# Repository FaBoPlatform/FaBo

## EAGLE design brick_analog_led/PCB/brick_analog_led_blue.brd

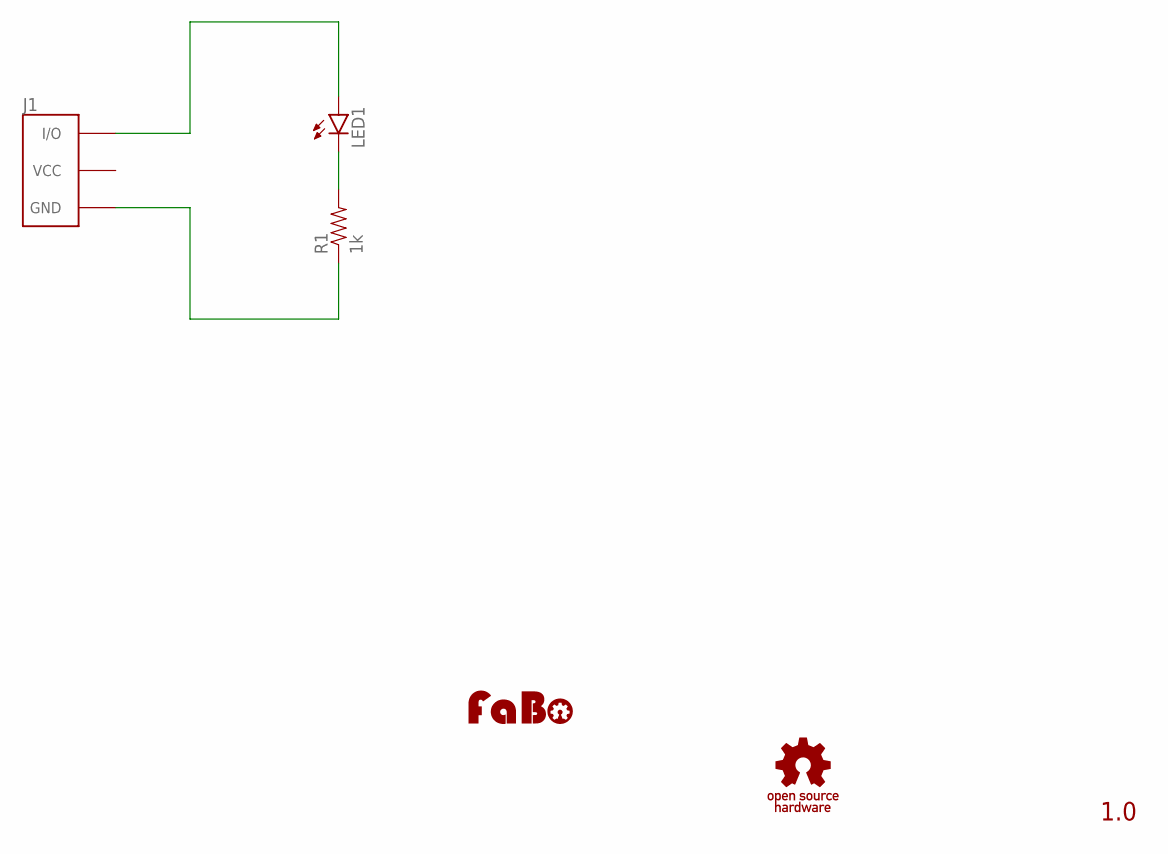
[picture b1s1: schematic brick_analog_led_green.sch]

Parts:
J1: BRICK_3PIN_NORMAL; BRICK_3PIN
LED1: LED-5MM
R1: 1k; RES-AXL-REGULAR
U$1: LOGO_FABO-M; LOGO_FABO_M
U$4: LOGO_OSHW_T-M; LOGO_OSHW_T_M

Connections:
GND: J1.GND, R1.P$1 (1)
unnamed: J1.IN/OUT (I/O), LED1.A
unnamed: LED1.K (C), R1.P$2 (2)

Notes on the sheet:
1.0

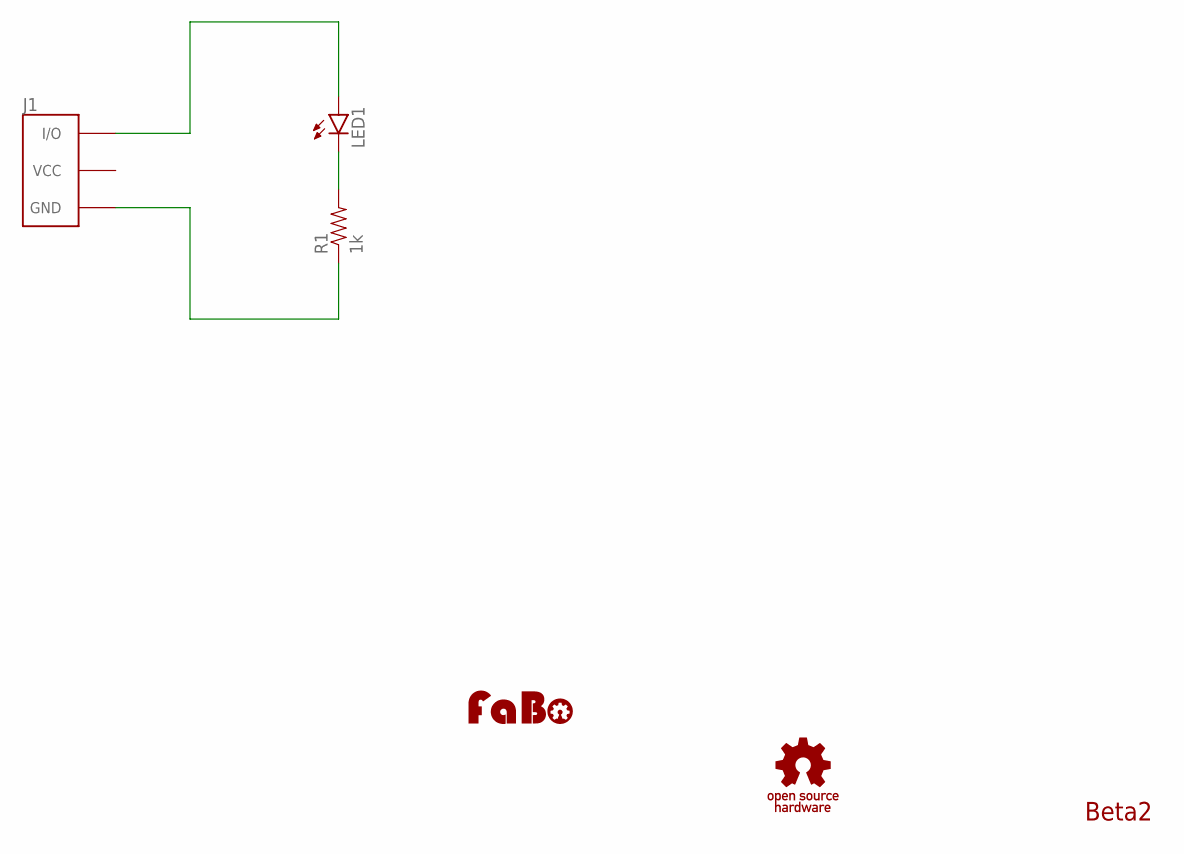
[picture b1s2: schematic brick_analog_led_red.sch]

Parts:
J1: BRICK_3PIN
LED1: LED-5MM
R1: 1k; RES-AXL-REGULAR
U$1: LOGO_FABO-M; LOGO_FABO_M
U$4: LOGO_OSHW_T-M; LOGO_OSHW_T_M

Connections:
GND: J1.GND, R1.P$1 (1)
unnamed: J1.IN/OUT (I/O), LED1.A
unnamed: LED1.K (C), R1.P$2 (2)

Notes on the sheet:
Beta2

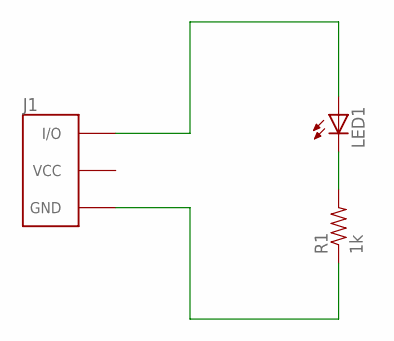
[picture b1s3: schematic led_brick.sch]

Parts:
J1: BRICK_3PIN
LED1: LED; LED5MM
R1: 1k; AXIAL-0.4

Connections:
GND: J1.GND, R1.P$1 (1)
unnamed: J1.IN/OUT (I/O), LED1.A
unnamed: LED1.K (C), R1.P$2 (2)

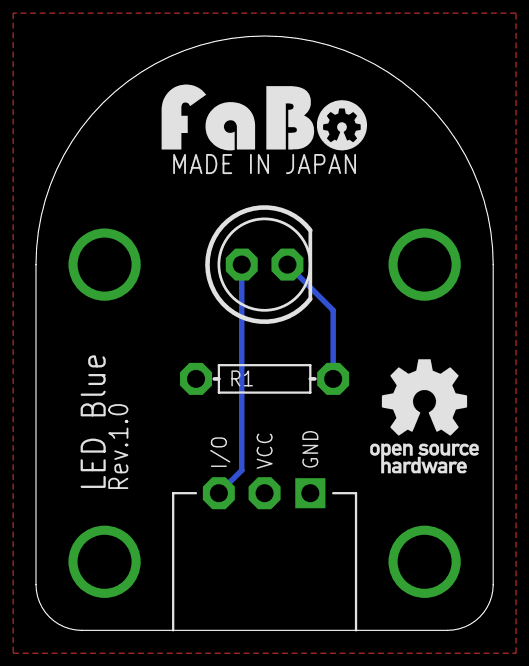
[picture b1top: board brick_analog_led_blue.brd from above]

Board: 2 copper layers, 25.4 x 33.0 mm, 5 parts (0 on the bottom side), 3 nets.

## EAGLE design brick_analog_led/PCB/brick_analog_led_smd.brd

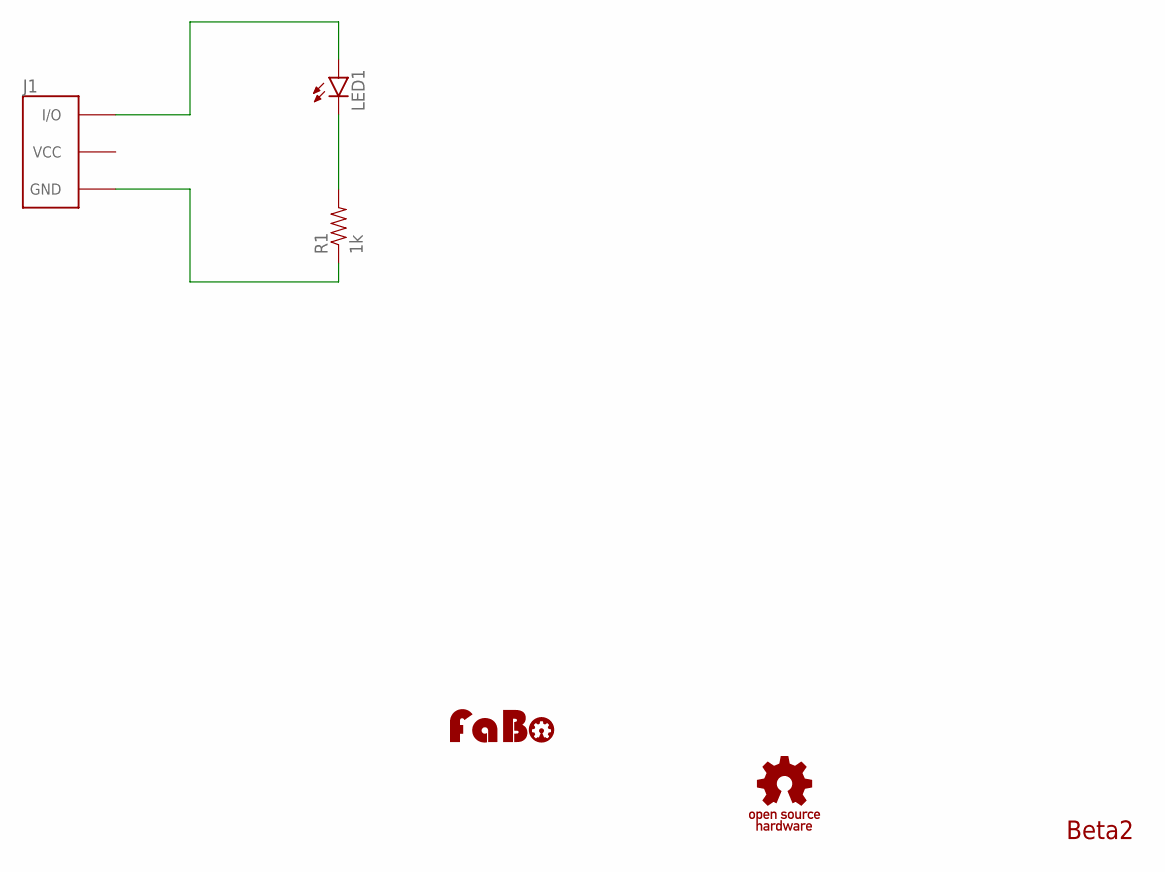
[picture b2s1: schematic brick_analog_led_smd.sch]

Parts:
J1: BRICK_3PIN
LED1: LED-EIA0603; EIA0603-LED
R1: 1k; EIA0603
U$2: LOGO_FABO-M; LOGO_FABO_M
U$4: LOGO_OSHW_T-M; LOGO_OSHW_T_M

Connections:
GND: J1.GND, R1.1
unnamed: J1.IN/OUT (I/O), LED1.A
unnamed: LED1.C, R1.2

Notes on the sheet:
Beta2

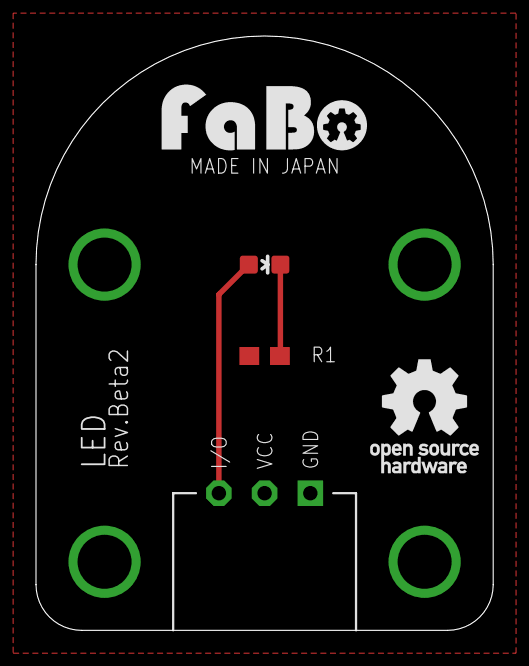
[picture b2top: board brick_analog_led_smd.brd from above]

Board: 2 copper layers, 25.4 x 33.0 mm, 5 parts (0 on the bottom side), 3 nets.

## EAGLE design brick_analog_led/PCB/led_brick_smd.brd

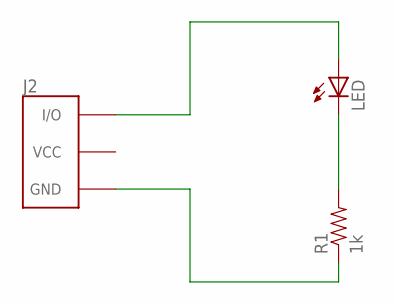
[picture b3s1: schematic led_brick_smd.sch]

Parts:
J2: BRICK_3PIN
LED: LED; CHIP-LED0603
R1: 1k; 0603-RES

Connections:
GND: J2.GND, R1.1
unnamed: J2.IN/OUT (I/O), LED.A
unnamed: LED.C, R1.2

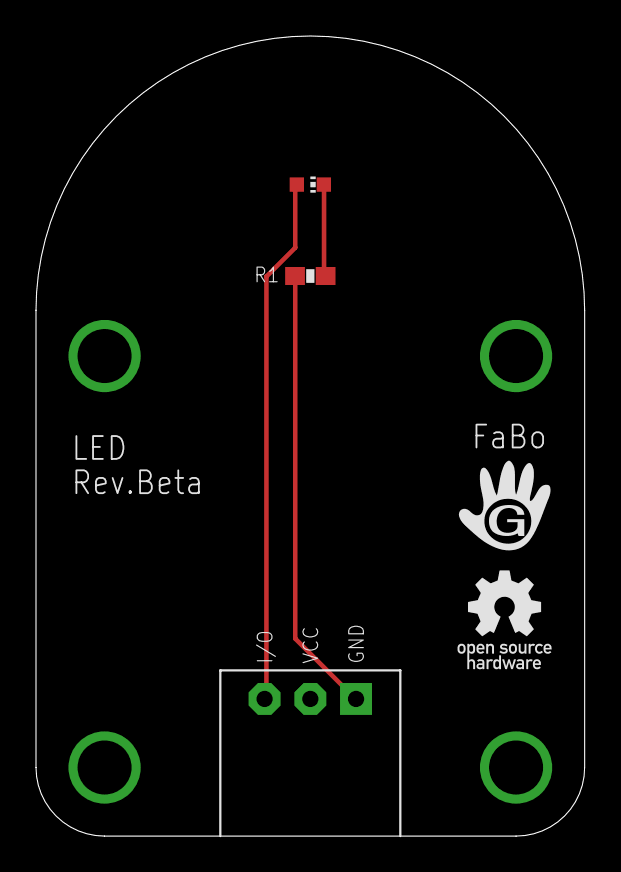
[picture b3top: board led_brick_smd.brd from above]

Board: 2 copper layers, 30.5 x 44.5 mm, 5 parts (0 on the bottom side), 3 nets.

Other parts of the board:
U$2: LOGO_GCLUE_M
U$3: LOGO_OSHW_T_M

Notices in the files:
parts and their libraries:
SparkFun-Resistors: Licensing: Creative Commons ShareAlike 4.0 International - https://creativecommons.org/licenses/by-sa/4.0
SparkFun: Licensing: CC v3.0 Share-Alike You are welcome to use this library for commercial purposes.
